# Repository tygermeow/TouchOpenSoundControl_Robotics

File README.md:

# TouchOpenSoundControl_Robotics

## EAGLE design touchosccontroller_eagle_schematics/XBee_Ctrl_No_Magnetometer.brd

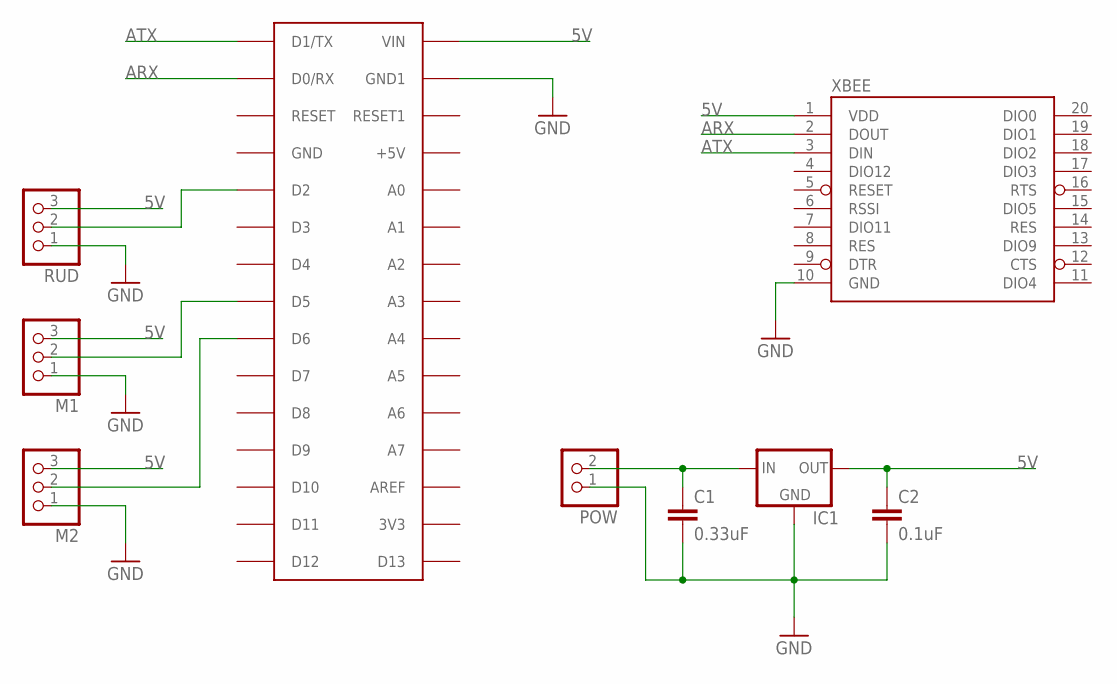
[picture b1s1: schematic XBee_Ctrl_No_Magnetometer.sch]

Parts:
C1: 0.33uF; C5B2.5
C2: 0.1uF; C5B2.5
IC1: 78XXL
M1, M2: PINHD-1X3; 1X03
NANO: ARDUINONANO; PDIP-32
POW: PINHD-1X2; 1X02
RUD: PINHD-1X3; 1X03
XBEE: XBEE-1B1; XBEE-1

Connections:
5V: C2.1, IC1.OUT, M1.3, M2.3, NANO.VIN, RUD.3, XBEE.1 (VDD)
ARX: NANO.D0/RX, XBEE.2 (DOUT)
ATX: NANO.D1/TX, XBEE.3 (DIN)
GND: C1.2, C2.2, IC1.GND, M1.1, M2.1, NANO.GND1, POW.1, RUD.1, XBEE.10 (GND)
unnamed: C1.1, IC1.IN, POW.2
unnamed: NANO.D2, RUD.2
unnamed: M1.2, NANO.D5
unnamed: M2.2, NANO.D6

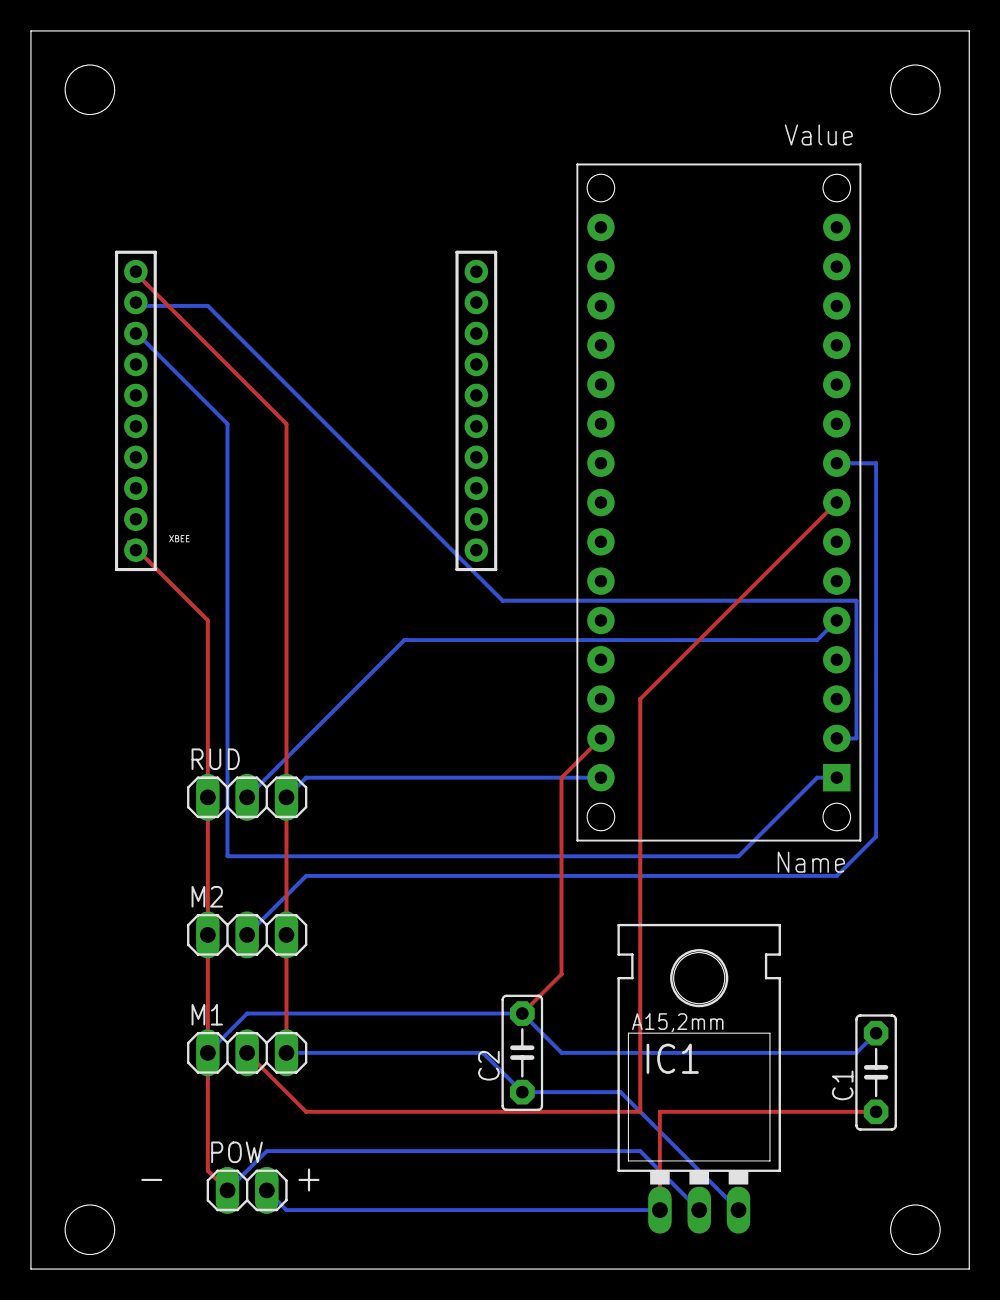
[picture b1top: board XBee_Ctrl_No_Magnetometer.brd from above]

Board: 2 copper layers, 60.6 x 80.0 mm, 9 parts (0 on the bottom side), 8 nets.

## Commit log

2016-06-22 Hello
2016-08-22 Commit controls
    Need to write up ready for instructions

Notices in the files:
parts and their libraries:
Sparkfun_RF: Licensing: Creative Commons ShareAlike 4.0 International - https://creativecommons.org/licenses/by-sa/4.0
